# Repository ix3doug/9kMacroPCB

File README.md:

# 9kMacroPCB
My First PCB Design for a 9 Key Macro Keyboard

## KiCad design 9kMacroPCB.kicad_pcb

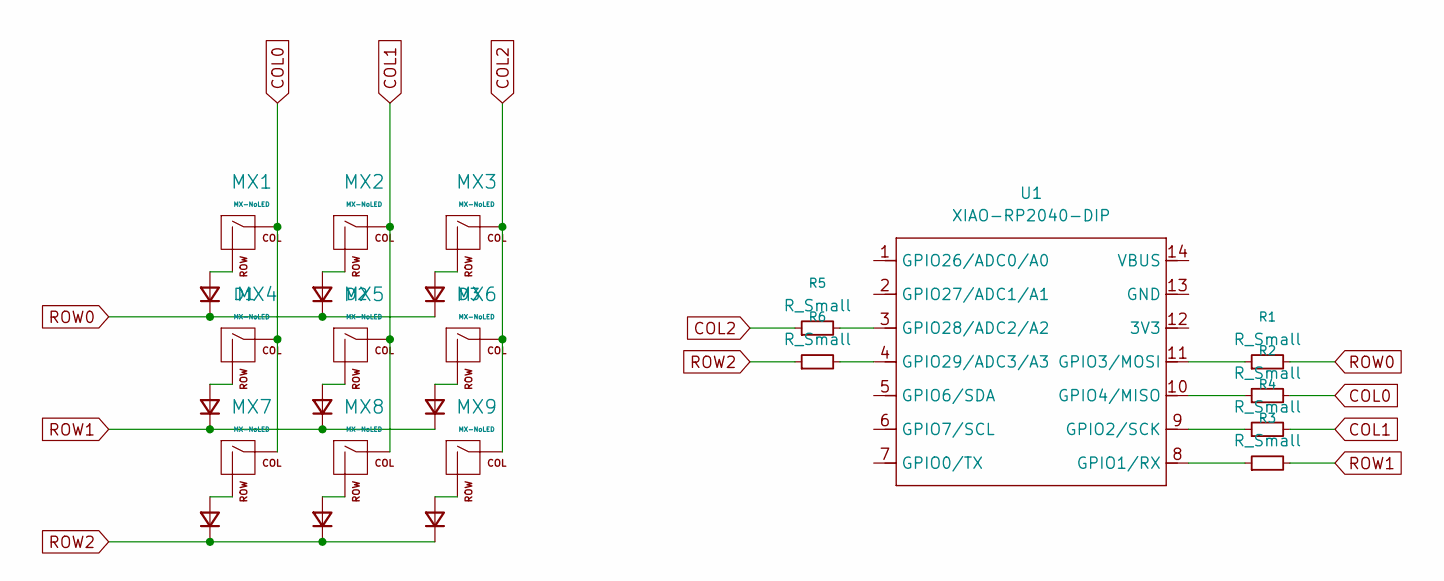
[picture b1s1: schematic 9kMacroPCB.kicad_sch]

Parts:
D1, D2, D3, D4, D5, D6, D7, D8, D9: D_Small; D_SOD-123
MX1, MX2, MX3, MX4, MX5, MX6, MX7, MX8, MX9: MX-NoLED; MX-1U-NoLED
R1, R2, R3, R4, R5, R6: R_Small; R_0805_2012Metric
U1: XIAO-RP2040-DIP

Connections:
COL0: MX1.1 (COL), MX4.1 (COL), MX7.1 (COL), R2.2
COL1: MX2.1 (COL), MX5.1 (COL), MX8.1 (COL), R4.2
COL2: MX3.1 (COL), MX6.1 (COL), MX9.1 (COL), R5.1
unnamed: D1.2 (A), MX1.2 (ROW)
unnamed: D2.2 (A), MX2.2 (ROW)
unnamed: D3.2 (A), MX3.2 (ROW)
unnamed: D4.2 (A), MX4.2 (ROW)
unnamed: D5.2 (A), MX5.2 (ROW)
unnamed: D6.2 (A), MX6.2 (ROW)
unnamed: D7.2 (A), MX7.2 (ROW)
unnamed: D8.2 (A), MX8.2 (ROW)
unnamed: D9.2 (A), MX9.2 (ROW)
unnamed: R3.1, U1.8 (GPIO1/RX)
unnamed: R4.1, U1.9 (GPIO2/SCK)
unnamed: R1.1, U1.11 (GPIO3/MOSI)
unnamed: R2.1, U1.10 (GPIO4/MISO)
unnamed: R5.2, U1.3 (GPIO28/ADC2/A2)
unnamed: R6.2, U1.4 (GPIO29/ADC3/A3)
ROW0: D1.1 (K), D2.1 (K), D3.1 (K), R1.2
ROW1: D4.1 (K), D5.1 (K), D6.1 (K), R3.2
ROW2: D7.1 (K), D8.1 (K), D9.1 (K), R6.1

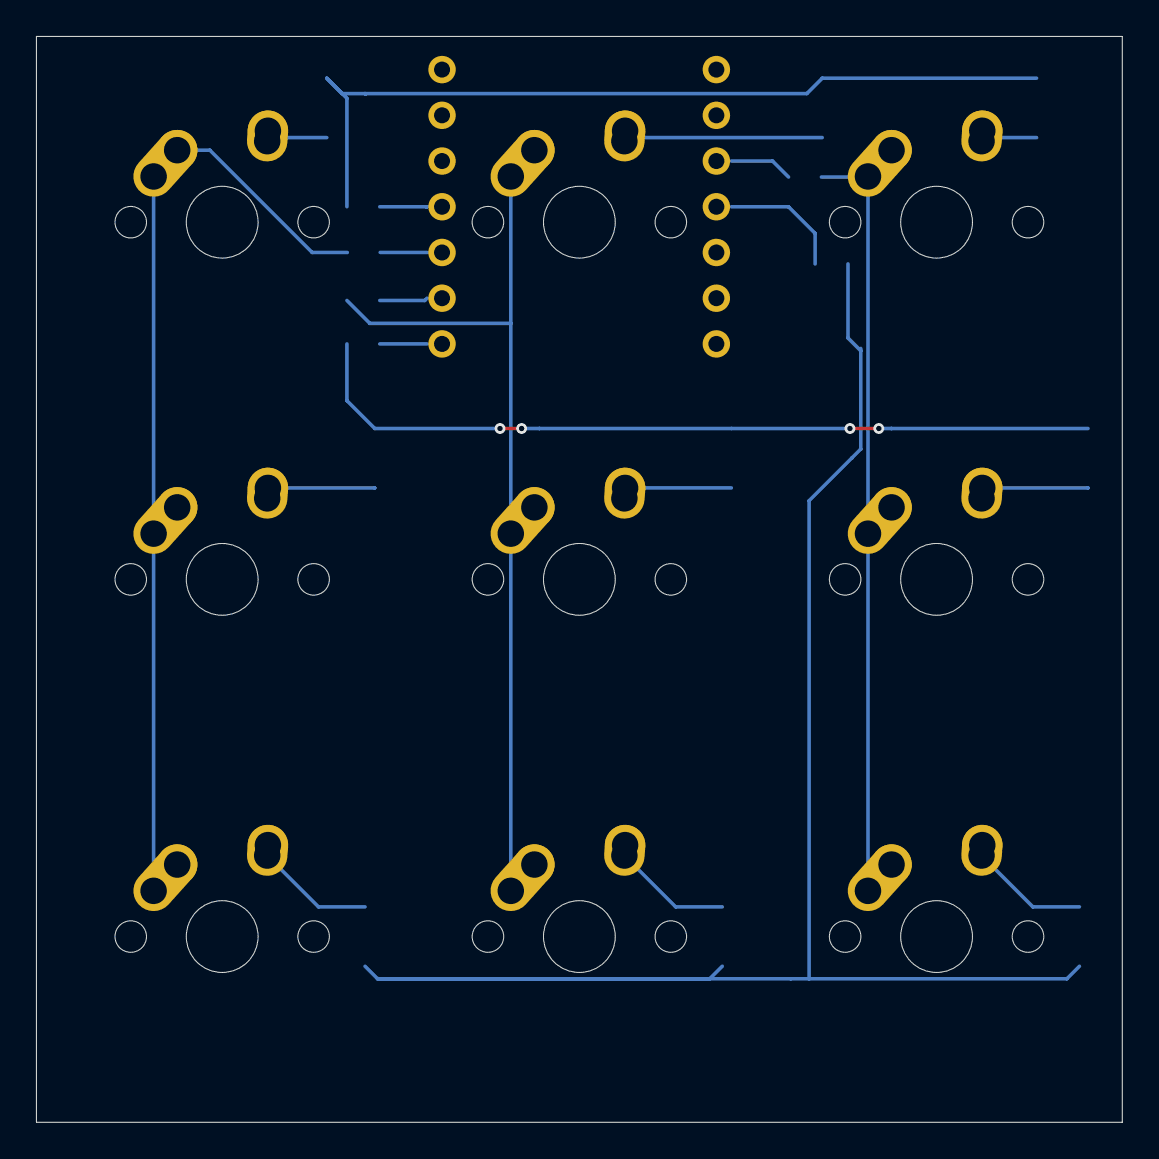
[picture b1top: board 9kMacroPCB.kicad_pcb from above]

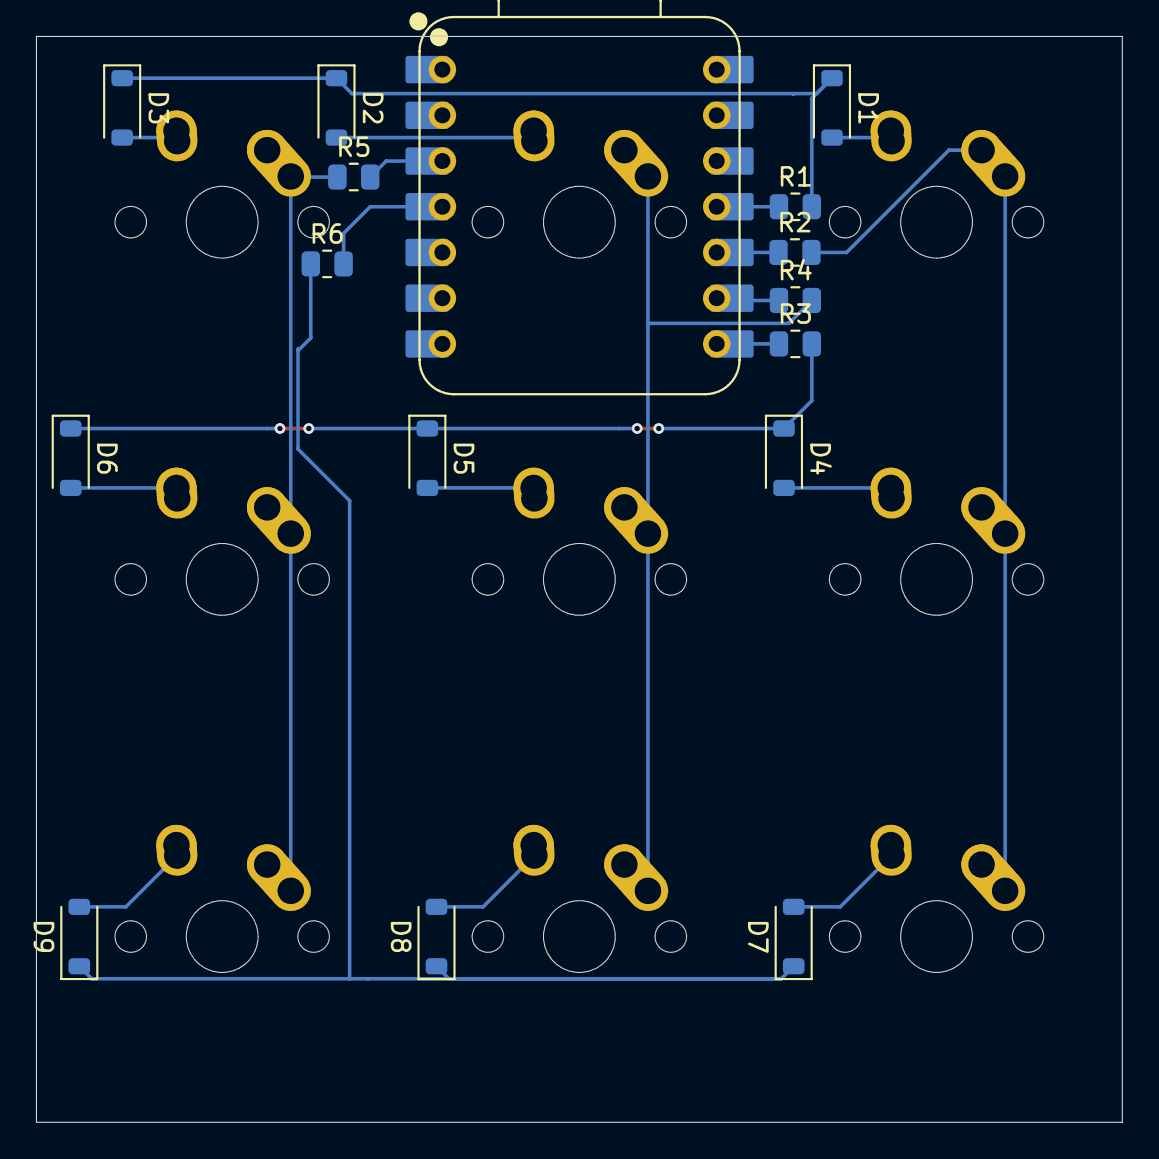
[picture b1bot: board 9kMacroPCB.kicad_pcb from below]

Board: 2 copper layers, 60.3 x 60.3 mm, 25 parts (16 on the bottom side), 21 nets.

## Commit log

2025-07-27 Add submodules
2025-07-27 Add control submodules
2025-07-27 updating base lib for pcb
    following ai03 tut
2025-07-27 Add Sw Matrix submodules
2025-07-27 PCB updates
    added PCB device libs and assigned footprints
2025-07-27 Add PCB layout and backup files for 9kMacroPCB
    Added and updated KiCad PCB, project, and prl files for the 9kMacroPCB, including new STEP model and multiple backup ZIPs.
2025-07-29 Remove OPL library, add XIAO RP2040 library, update schematic
    Removed the OPL_Kicad_Library submodule and added Seeeduino XIAO RP2040 KiCAD symbol and footprint libraries. Updated 9kMacroPCB.kicad_sch to remove R_Small resistors and references to the OPL librar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
2025-07-29 Update PCB: netlist, footprints, and backup cleanup
    Removed old backup zip files and added an auto-saved file reference. Updated net assignments and pin naming in 9kMacroPCB.kicad_pcb, made significant changes to footprints (notably D1, R4, and U1), a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
2025-07-29 Update PCB export settings and regenerate outputs
    Changed PCB export settings to output files to the EXPORTS directory and adjusted drill shape settings. Removed old STEP and lock files, and added new Gerber, STEP, and image exports to the EXPORTS d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
